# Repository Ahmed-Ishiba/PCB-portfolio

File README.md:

# PCB-portfolio
This repository showcases a collection of electronics projects I designed, simulated, and tested

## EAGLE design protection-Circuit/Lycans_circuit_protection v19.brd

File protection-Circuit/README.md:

# Protection circuit board
I designed this PCB as a part of an exercise in my university technical team 

this board realies on an eFuse (TPS26630) to protect UAV components from:
- Reverse Polarity
- Over-current / short-circuit protection
- Inrush current (hot-plug)
- Over-voltage and under-voltage lockout
- Transient suppression (ESD/inductive kick)

The board is purposly stretched out because I needed to present each component and its use

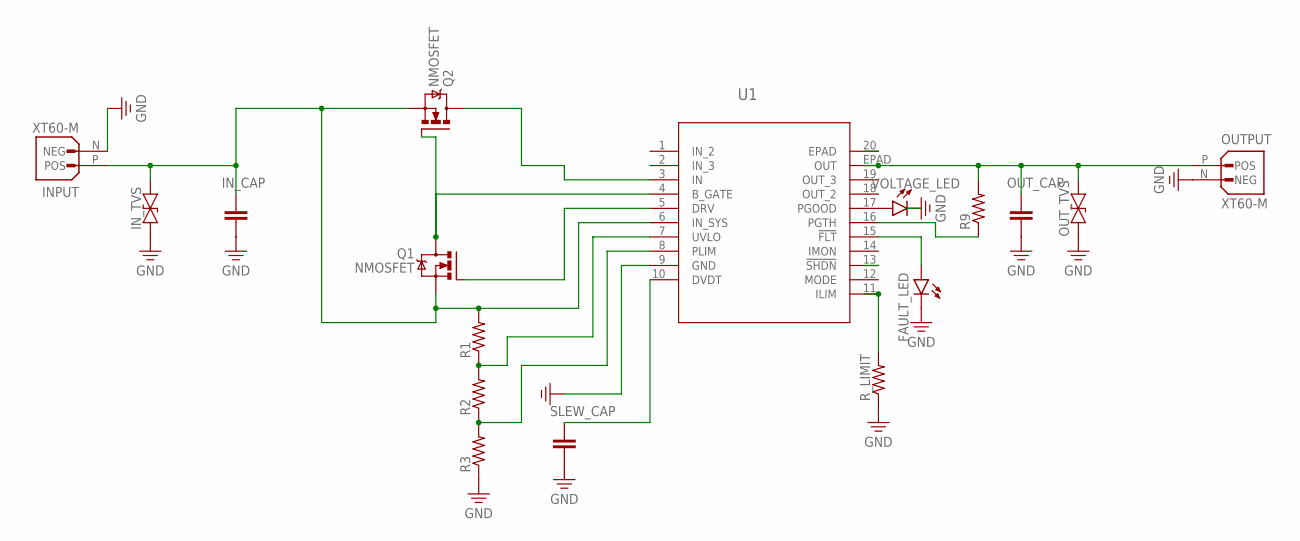
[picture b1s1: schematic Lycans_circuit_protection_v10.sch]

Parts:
FAULT_LED: LED_WHITE; LEDRD254W60D565H860B_W
INPUT: XT60-M; AMASS_XT60-M
IN_CAP: CC0805KRX7R9BB104; CAP_0805
IN_TVS: TVS_SMAJ*_DO-214AC(SMA); DIOM5226X290N
OUTPUT: XT60-M; AMASS_XT60-M
OUT_CAP: CC0805KRX7R9BB104; CAP_0805
OUT_TVS: TVS_SMAJ*_DO-214AC(SMA); DIOM5226X290N
Q1, Q2: NMOSFET; SOT23
R1, R2, R3, R9: CRCW08050000Z0EA; RES_0805
R_LIMIT: CRCW08050000Z0EA; RES_0805
SLEW_CAP: CC0805KRX7R9BB104; CAP_0805
U1: TPS26636PWPRHTSSOP20_PWP_TEX-M; HTSSOP20_PWP_TEX-M
VOLTAGE_LED: LED_WHITE; LEDRD254W60D565H860B_W

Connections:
GND: FAULT_LED.2 (C), INPUT.N (NEG), IN_CAP.2, IN_TVS.1, OUTPUT.N (NEG), OUT_CAP.2, OUT_TVS.1, R3.1, R_LIMIT.1, SLEW_CAP.2, U1.9 (GND), VOLTAGE_LED.2 (C)
IN_2: U1.1 (IN_2)
IN_3: U1.2 (IN_3)
unnamed: INPUT.P (POS), IN_CAP.1, IN_TVS.2, Q1.2 (S), Q2.2 (S), R1.2, U1.6 (IN_SYS)
unnamed: R_LIMIT.2, U1.11 (ILIM)
unnamed: Q2.3 (D), U1.3 (IN)
unnamed: SLEW_CAP.1, U1.10 (DVDT)
unnamed: Q1.1 (G), U1.5 (DRV)
unnamed: R1.1, R2.2, U1.7 (UVLO)
unnamed: R2.1, R3.2, U1.8 (PLIM)
unnamed: U1.17 (PGOOD), VOLTAGE_LED.1 (A)
unnamed: FAULT_LED.1 (A), U1.15 (!FLT)
unnamed: R9.1, U1.16 (PGTH)
unnamed: Q1.3 (D), Q2.1 (G), U1.4 (B_GATE)
unnamed: OUTPUT.P (POS), OUT_CAP.1, OUT_TVS.2, R9.2, U1.EPAD (OUT)
OUT_2: U1.18 (OUT_2)
OUT_3: U1.19 (OUT_3)

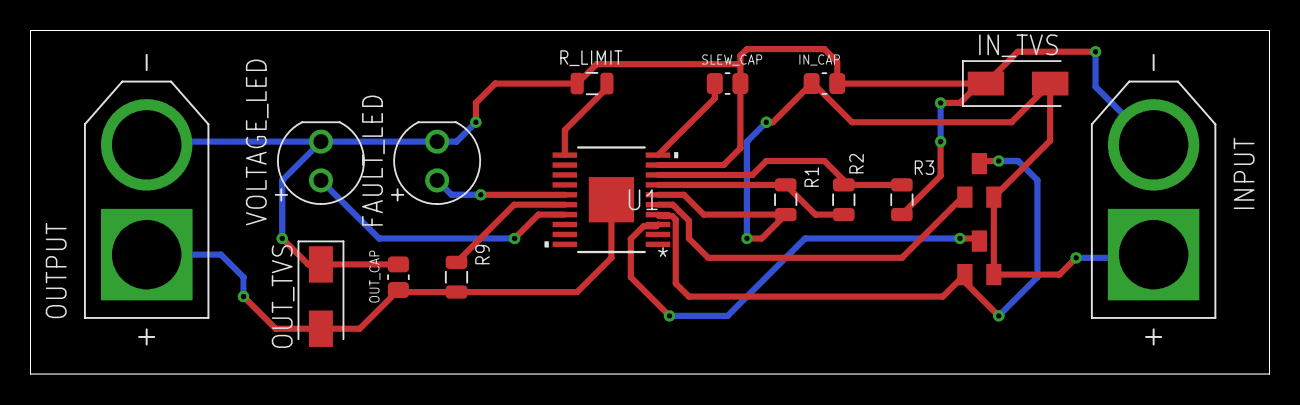
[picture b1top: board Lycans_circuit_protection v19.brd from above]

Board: 2 copper layers, 81.3 x 22.5 mm, 17 parts (0 on the bottom side), 13 nets.

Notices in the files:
parts and their libraries:
COPYRIGHT: Copyright (C) 2025 Ultra Librarian. All rights reserved.
